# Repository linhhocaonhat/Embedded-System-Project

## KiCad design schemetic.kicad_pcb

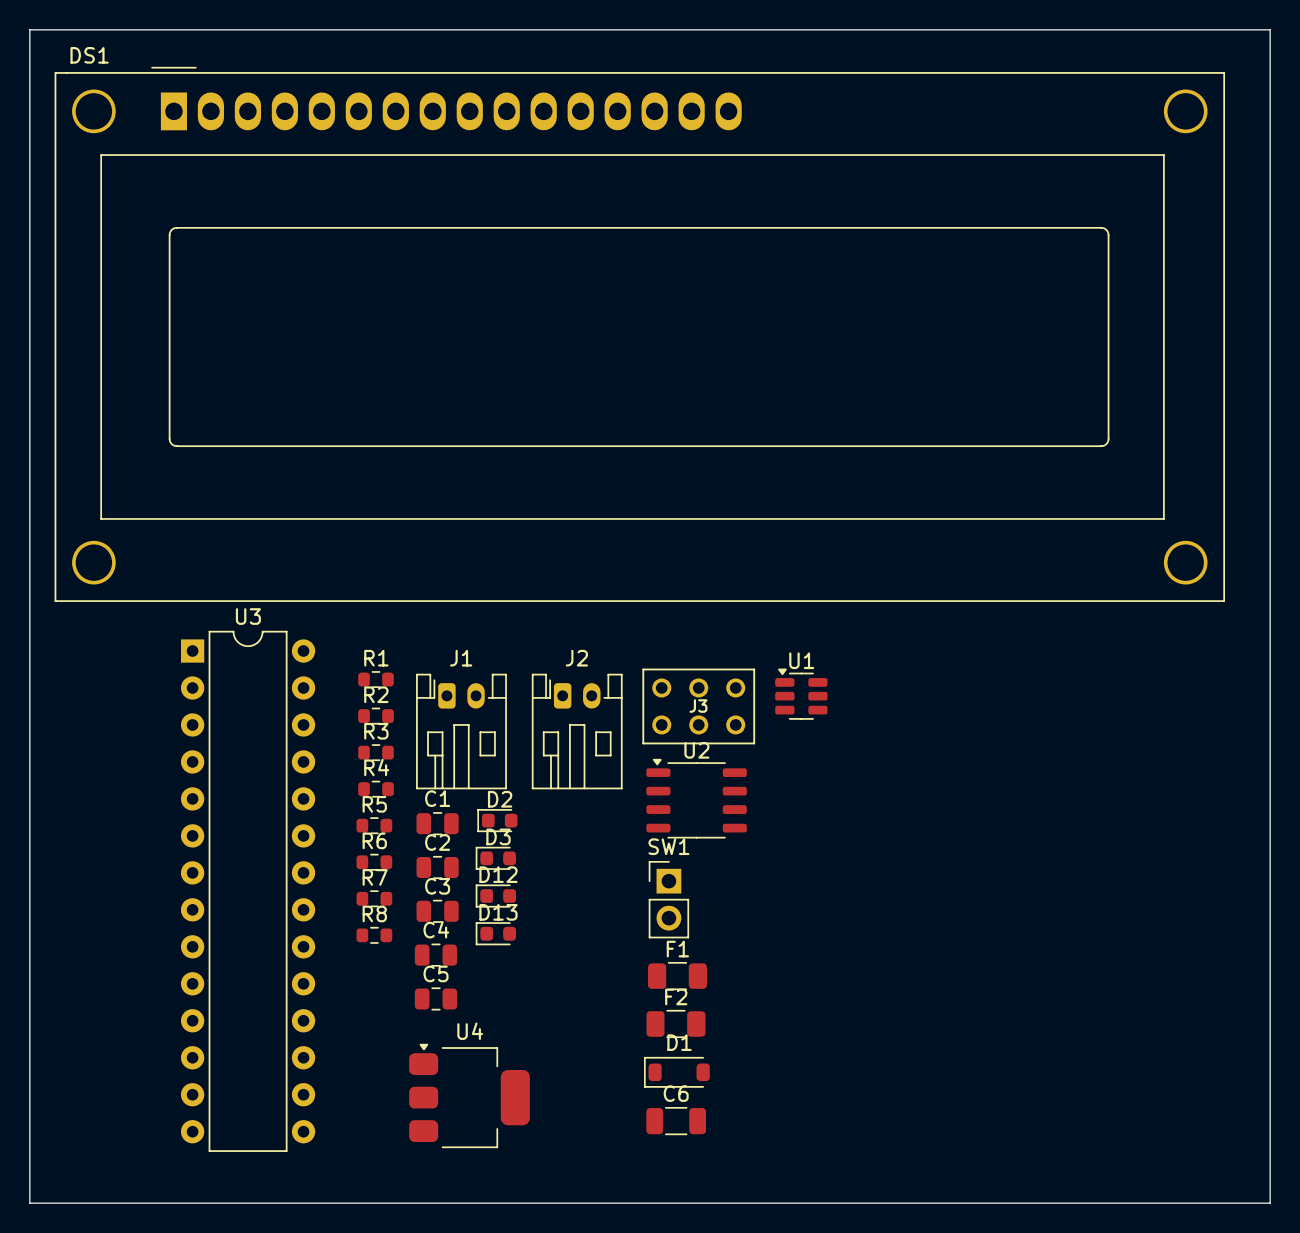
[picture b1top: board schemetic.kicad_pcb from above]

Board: 2 copper layers, 85.2 x 80.6 mm, 30 parts (0 on the bottom side), 33 nets, no tracks yet.

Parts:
C1: 10uF; C_0805_2012Metric
C2: 10nF; C_0805_2012Metric
C3: 22uF; C_0805_2012Metric
C4: 0.1uF; C_0805_2012Metric
C5: 1uF; C_0805_2012Metric
C6: 47uF; C_1206_3216Metric
D1: B5819W; D_SOD-123
D2: YELLOW; LED_0603_1608Metric
D3: GREEN; LED_0603_1608Metric
D12: LED_GREEN; LED_0603_1608Metric
D13: LED_RED; LED_0603_1608Metric
DS1: WC1602A
F1, F2: 750mA; Fuse_1206_3216Metric
J1: BattConn1; JST_PH_S2B-PH-K_1x02_P2.00mm_Horizontal
J2: BattConn0; JST_PH_S2B-PH-K_1x02_P2.00mm_Horizontal
J3: AVR-ISP-6; AVR-ISP
R1: 100k; R_0603_1608Metric
R2: 49.9k; R_0603_1608Metric
R3: 9.53k; R_0603_1608Metric
R4, R6: 1k; R_0603_1608Metric
R5: 1; R_0603_1608Metric
R7, R8: R_Small_US; R_0603_1608Metric
SW1: SW_SPST; PinHeader_1x02_P2.54mm_Vertical
U1: MP2359; TSOT-23-6
U2: RS3E075AT; SOP-8_3.9x4.9mm_P1.27mm
U3: ATmega328-P; DIP-28_W7.62mm
U4: AMS1117-3.3; SOT-223-3_TabPin2

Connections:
+3V3: R5.2, R6.2, U4.2 (VO)
+5V: C3.1, D12.2 (A), D13.2 (A), DS1.2 (VDD), F2.1, R2.1, R4.1, U3.7 (VCC), U3.20 (AVCC)
+BATT: F1.1, U2.1 (S), U2.2 (S), U2.3 (S)
/COLUMN_0: U3.1 (~RESET/PC6), U3.23 (PC0), U3.24 (PC1), U3.25 (PC2)
/ENABLE: DS1.6 (E), U3.14 (PB0)
/LCD0: DS1.7 (D0), U3.2 (PD0)
/LCD1: DS1.8 (D1), U3.3 (PD1)
/LCD2: DS1.9 (D2), U3.4 (PD2)
/LCD3: DS1.10 (D3), U3.5 (PD3)
/LCD4: DS1.11 (D4), U3.6 (PD4)
/LCD5: DS1.12 (D5), U3.11 (PD5)
/LCD6: DS1.13 (D6), U3.12 (PD6)
/LCD7: DS1.14 (D7), U3.13 (PD7)
/LED_GREEN: R7.1, U3.9 (XTAL1/PB6)
/LED_RED: R8.1, U3.10 (XTAL2/PB7)
/RS: DS1.4 (RS), U3.16 (PB2)
/R/W: DS1.5 (R/W), U3.15 (PB1)
GND: C1.2, C3.2, C4.1, C5.2, C6.2, D1.2 (A), D2.1 (K), D3.1 (K), DS1.1 (VSS), DS1.3 (VO), J2.2, R3.2, U1.2 (GND), U2.4 (G), U3.8 (GND), U3.22 (GND), U4.1 (GND)
unnamed: C6.1, R5.1
unnamed: C2.2, D1.1 (K), U1.6 (SW)
unnamed: D2.2 (A), R4.2
unnamed: D3.2 (A), R6.1
unnamed: D12.1 (K), R7.2
unnamed: D13.1 (K), R8.2
unnamed: J1.1, SW1.1 (A)
unnamed: J1.2, J2.1
unnamed: SW1.2 (B), U2.5 (D), U2.6 (D), U2.7 (D), U2.8 (D)
unnamed: C2.1, U1.1 (BST)
unnamed: R1.2, U1.4 (EN)
unnamed: R2.2, R3.1, U1.3 (FB)
unnamed: C1.1, F1.2, R1.1, U1.5 (IN)
unnamed: C4.2, U3.21 (AREF)
unnamed: C5.1, F2.2, U4.3 (VI)
